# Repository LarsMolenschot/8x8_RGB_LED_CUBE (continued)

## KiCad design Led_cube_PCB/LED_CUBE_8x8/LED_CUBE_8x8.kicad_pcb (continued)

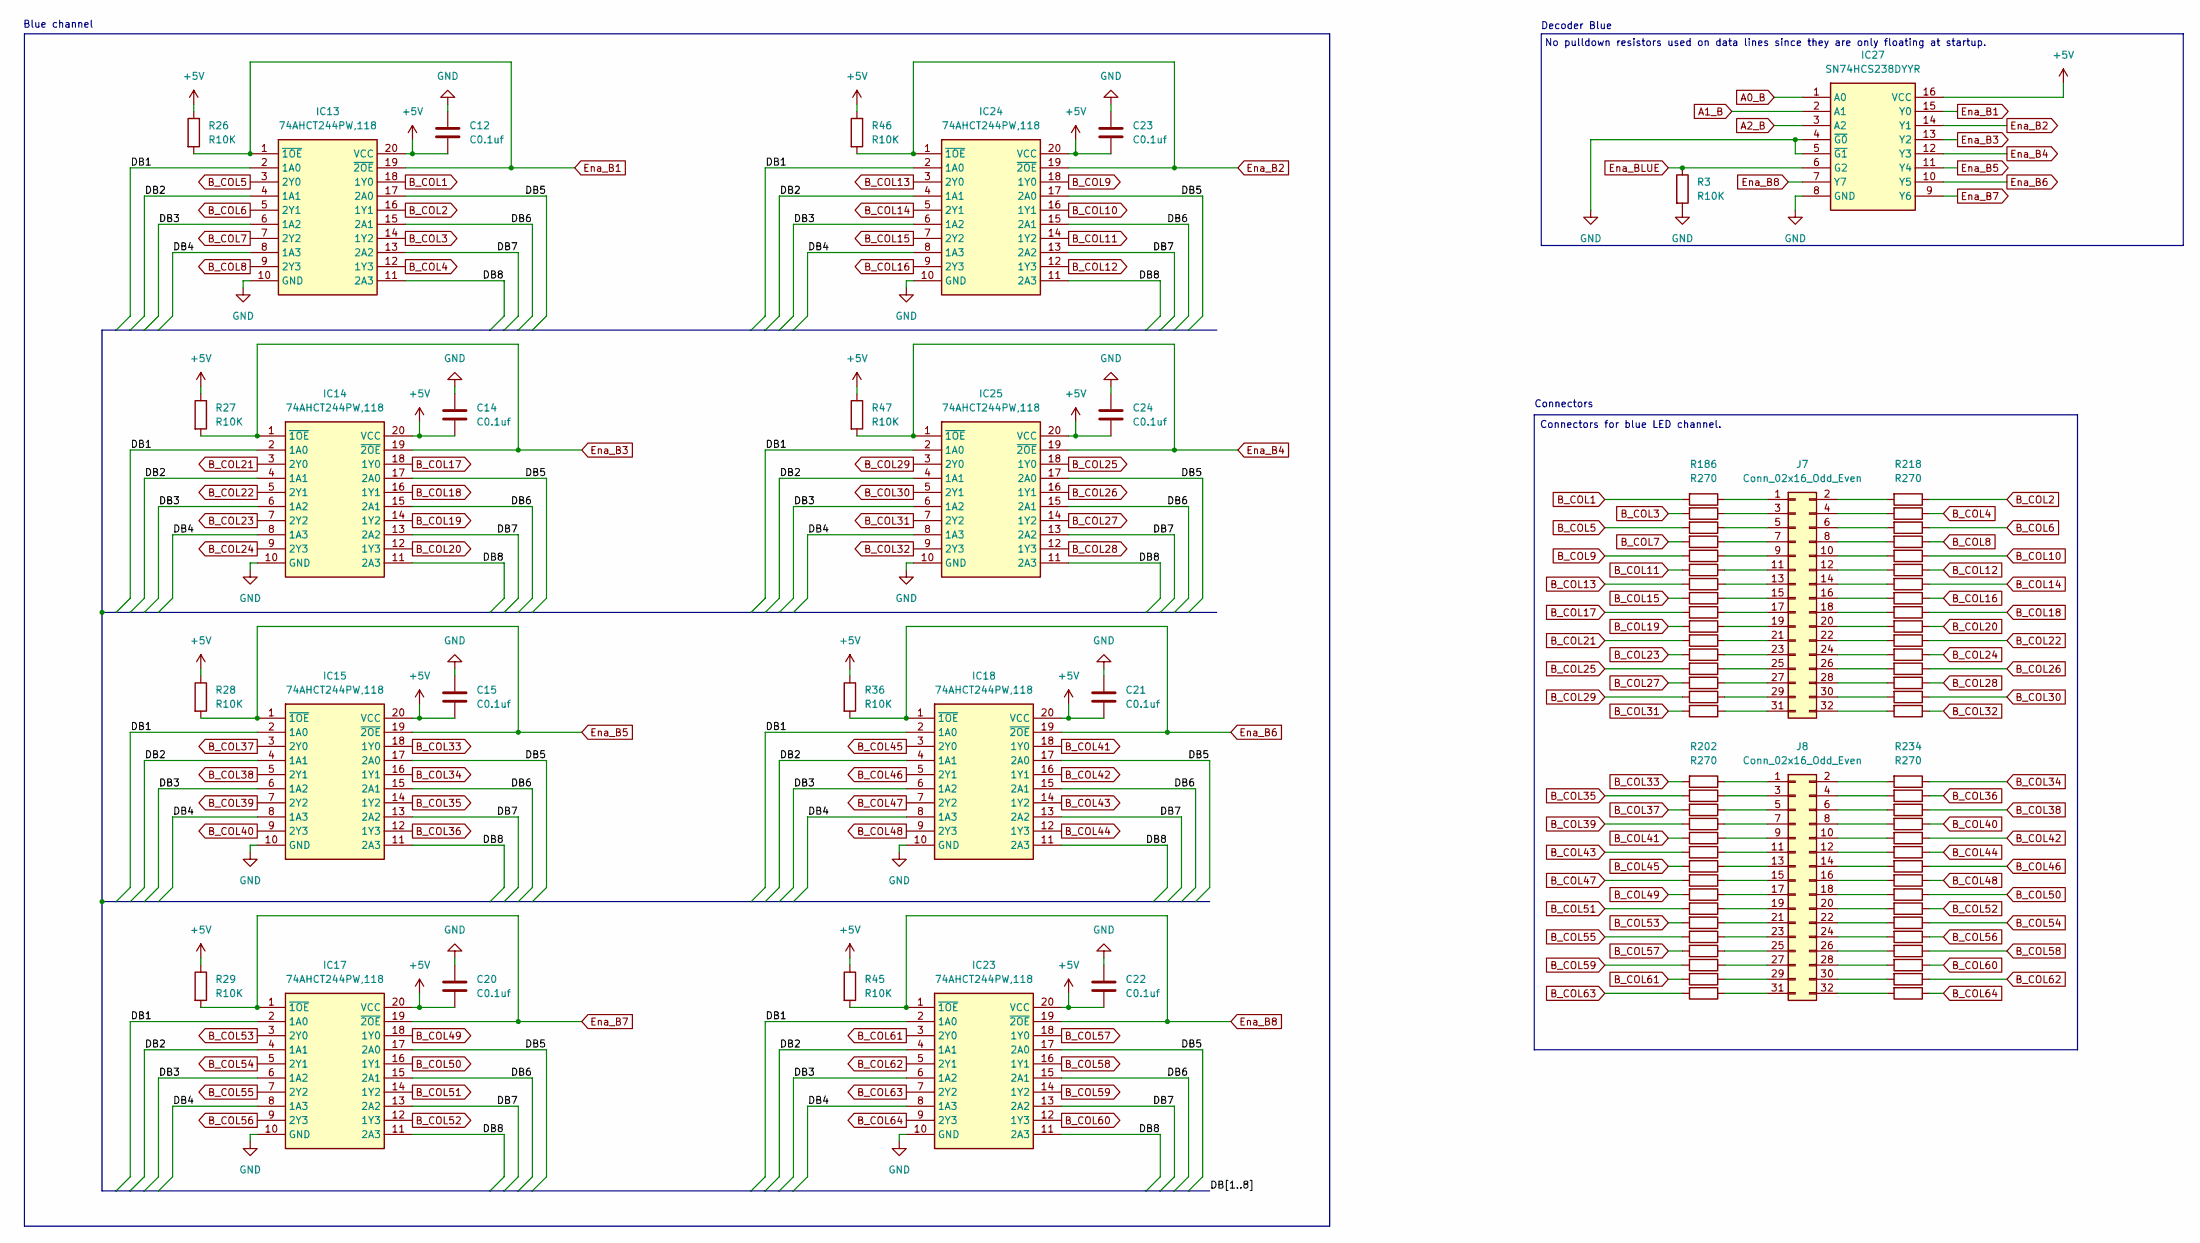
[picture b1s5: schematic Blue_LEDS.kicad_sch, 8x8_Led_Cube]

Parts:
C12, C14, C15, C20, C21, C22, C23, C24: C0.1uf; C_0603_1608Metric_Pad1.08x0.95mm_HandSolder
IC13, IC14, IC15, IC17, IC18, IC23, IC24, IC25: 74AHCT244PW,118; SOP65P640X110-20N; Mouser Part Number 771-AHCT244PW118
IC27: SN74HCS238DYYR; SOP50P326X110-16N; Mouser Part Number 595-SN74HCS238DYYR
J7, J8: Conn_02x16_Odd_Even; PinSocket_2x16_P2.54mm_Vertical
R3, R26, R27, R28, R29, R36, R45, R46, R47: R10K; R_0603_1608Metric_Pad0.98x0.95mm_HandSolder
R186, R187, R188, R189, R190, R191, R192, R193, R194, R195, R196, R197, R198, R199, R200, R201, R202, R203, R204, R205, R206, R207, R208, R209, R210, R211, R212, R213, R214, R215, R216, R217, R218, R219, R220, R221, R222, R223, R224, R225, R226, R227, R228, R229, R230, R231, R232, R233, R234, R235, R236, R237, R238, R239, R240, R241, R242, R243, R244, R245, R246, R247, R248, R249: R270; R_0603_1608Metric_Pad0.98x0.95mm_HandSolder

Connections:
+5V: C12.2, C14.2, C15.2, C20.2, C21.2, C22.2, C23.2, C24.1, IC13.20 (VCC), IC14.20 (VCC), IC15.20 (VCC), IC17.20 (VCC), IC18.20 (VCC), IC23.20 (VCC), IC24.20 (VCC), IC25.20 (VCC), IC27.16 (VCC), R26.1, R27.1, R28.1, R29.1, R36.1, R45.1, R46.1, R47.1; also elsewhere on the board
/Blue LED's/DB1: IC13.2 (1A0), IC14.2 (1A0), IC15.2 (1A0), IC17.2 (1A0), IC18.2 (1A0), IC23.2 (1A0), IC24.2 (1A0), IC25.2 (1A0)
/Blue LED's/DB2: IC13.4 (1A1), IC14.4 (1A1), IC15.4 (1A1), IC17.4 (1A1), IC18.4 (1A1), IC23.4 (1A1), IC24.4 (1A1), IC25.4 (1A1)
/Blue LED's/DB3: IC13.6 (1A2), IC14.6 (1A2), IC15.6 (1A2), IC17.6 (1A2), IC18.6 (1A2), IC23.6 (1A2), IC24.6 (1A2), IC25.6 (1A2)
/Blue LED's/DB4: IC13.8 (1A3), IC14.8 (1A3), IC15.8 (1A3), IC17.8 (1A3), IC18.8 (1A3), IC23.8 (1A3), IC24.8 (1A3), IC25.8 (1A3)
/Blue LED's/DB5: IC13.17 (2A0), IC14.17 (2A0), IC15.17 (2A0), IC17.17 (2A0), IC18.17 (2A0), IC23.17 (2A0), IC24.17 (2A0), IC25.17 (2A0)
/Blue LED's/DB6: IC13.15 (2A1), IC14.15 (2A1), IC15.15 (2A1), IC17.15 (2A1), IC18.15 (2A1), IC23.15 (2A1), IC24.15 (2A1), IC25.15 (2A1)
/Blue LED's/DB7: IC13.13 (2A2), IC14.13 (2A2), IC15.13 (2A2), IC17.13 (2A2), IC18.13 (2A2), IC23.13 (2A2), IC24.13 (2A2), IC25.13 (2A2)
/Blue LED's/DB8: IC13.11 (2A3), IC14.11 (2A3), IC15.11 (2A3), IC17.11 (2A3), IC18.11 (2A3), IC23.11 (2A3), IC24.11 (2A3), IC25.11 (2A3)
A0_B: IC27.1 (A0); also elsewhere on the board
A1_B: IC27.2 (A1); also elsewhere on the board
A2_B: IC27.3 (A2); also elsewhere on the board
B_COL1: IC13.18 (1Y0), R186.2
B_COL2: IC13.16 (1Y1), R218.1
B_COL3: IC13.14 (1Y2), R187.2
B_COL4: IC13.12 (1Y3), R219.1
B_COL5: IC13.3 (2Y0), R188.2
B_COL6: IC13.5 (2Y1), R220.1
B_COL7: IC13.7 (2Y2), R189.2
B_COL8: IC13.9 (2Y3), R221.1
B_COL9: IC24.18 (1Y0), R190.2
B_COL10: IC24.16 (1Y1), R222.1
B_COL11: IC24.14 (1Y2), R191.2
B_COL12: IC24.12 (1Y3), R223.1
B_COL13: IC24.3 (2Y0), R192.2
B_COL14: IC24.5 (2Y1), R224.1
B_COL15: IC24.7 (2Y2), R193.2
B_COL16: IC24.9 (2Y3), R225.1
B_COL17: IC14.18 (1Y0), R194.2
B_COL18: IC14.16 (1Y1), R226.1
B_COL19: IC14.14 (1Y2), R195.2
B_COL20: IC14.12 (1Y3), R227.1
B_COL21: IC14.3 (2Y0), R196.2
B_COL22: IC14.5 (2Y1), R228.1
B_COL23: IC14.7 (2Y2), R197.2
B_COL24: IC14.9 (2Y3), R229.1
B_COL25: IC25.18 (1Y0), R198.2
B_COL26: IC25.16 (1Y1), R230.1
B_COL27: IC25.14 (1Y2), R199.2
B_COL28: IC25.12 (1Y3), R231.1
B_COL29: IC25.3 (2Y0), R200.2
B_COL30: IC25.5 (2Y1), R232.1
B_COL31: IC25.7 (2Y2), R201.2
B_COL32: IC25.9 (2Y3), R233.1
B_COL33: IC15.18 (1Y0), R202.2
B_COL34: IC15.16 (1Y1), R234.1
B_COL35: IC15.14 (1Y2), R203.2
B_COL36: IC15.12 (1Y3), R235.1
B_COL37: IC15.3 (2Y0), R204.2
B_COL38: IC15.5 (2Y1), R236.1
B_COL39: IC15.7 (2Y2), R205.2
B_COL40: IC15.9 (2Y3), R237.1
B_COL41: IC18.18 (1Y0), R206.2
B_COL42: IC18.16 (1Y1), R238.1
B_COL43: IC18.14 (1Y2), R207.2
B_COL44: IC18.12 (1Y3), R239.1
B_COL45: IC18.3 (2Y0), R208.2
B_COL46: IC18.5 (2Y1), R240.1
B_COL47: IC18.7 (2Y2), R209.2
B_COL48: IC18.9 (2Y3), R241.1
B_COL49: IC17.18 (1Y0), R210.2
B_COL50: IC17.16 (1Y1), R242.1
B_COL51: IC17.14 (1Y2), R211.2
B_COL52: IC17.12 (1Y3), R243.1
B_COL53: IC17.3 (2Y0), R212.2
B_COL54: IC17.5 (2Y1), R244.1
B_COL55: IC17.7 (2Y2), R213.2
B_COL56: IC17.9 (2Y3), R245.1
B_COL57: IC23.18 (1Y0), R214.2
B_COL58: IC23.16 (1Y1), R246.1
B_COL59: IC23.14 (1Y2), R215.2
B_COL60: IC23.12 (1Y3), R247.1
B_COL61: IC23.3 (2Y0), R216.2
B_COL62: IC23.5 (2Y1), R248.1
B_COL63: IC23.7 (2Y2), R217.2
B_COL64: IC23.9 (2Y3), R249.1
Ena_B1: IC13.1 (~1OE), IC13.19 (~2OE), IC27.15 (Y0), R26.2
Ena_B2: IC24.1 (~1OE), IC24.19 (~2OE), IC27.14 (Y1), R46.2
Ena_B3: IC14.1 (~1OE), IC14.19 (~2OE), IC27.13 (Y2), R27.2
Ena_B4: IC25.1 (~1OE), IC25.19 (~2OE), IC27.12 (Y3), R47.2
Ena_B5: IC15.1 (~1OE), IC15.19 (~2OE), IC27.11 (Y4), R28.2
Ena_B6: IC18.1 (~1OE), IC18.19 (~2OE), IC27.10 (Y5), R36.2
Ena_B7: IC17.1 (~1OE), IC17.19 (~2OE), IC27.9 (Y6), R29.2
Ena_B8: IC23.1 (~1OE), IC23.19 (~2OE), IC27.7 (Y7), R45.2
Ena_BLUE: IC27.6 (G2), R3.1
GND: C12.1, C14.1, C15.1, C20.1, C21.1, C22.1, C23.1, C24.2, IC13.10 (GND), IC14.10 (GND), IC15.10 (GND), IC17.10 (GND), IC18.10 (GND), IC23.10 (GND), IC24.10 (GND), IC25.10 (GND), IC27.4 (~G0), IC27.5 (~G1), IC27.8 (GND), R3.2; also elsewhere on the board
unnamed: J7.1, R186.1
unnamed: J7.2, R218.2
unnamed: J7.3, R187.1
unnamed: J7.4, R219.2
unnamed: J7.5, R188.1
unnamed: J7.6, R220.2
unnamed: J7.7, R189.1
unnamed: J7.8, R221.2
unnamed: J7.9, R190.1
unnamed: J7.10, R222.2
unnamed: J7.11, R191.1
unnamed: J7.12, R223.2
unnamed: J7.13, R192.1
unnamed: J7.14, R224.2
unnamed: J7.15, R193.1
unnamed: J7.16, R225.2
unnamed: J7.17, R194.1
unnamed: J7.18, R226.2
unnamed: J7.19, R195.1
unnamed: J7.20, R227.2
unnamed: J7.21, R196.1
unnamed: J7.22, R228.2
unnamed: J7.23, R197.1
unnamed: J7.24, R229.2
unnamed: J7.25, R198.1
unnamed: J7.26, R230.2
unnamed: J7.27, R199.1
unnamed: J7.28, R231.2
unnamed: J7.29, R200.1
unnamed: J7.30, R232.2
unnamed: J7.31, R201.1
unnamed: J7.32, R233.2
unnamed: J8.1, R202.1
unnamed: J8.2, R234.2
unnamed: J8.3, R203.1
unnamed: J8.4, R235.2
unnamed: J8.5, R204.1
unnamed: J8.6, R236.2
unnamed: J8.7, R205.1
unnamed: J8.8, R237.2
unnamed: J8.9, R206.1
unnamed: J8.10, R238.2
unnamed: J8.11, R207.1
unnamed: J8.12, R239.2
unnamed: J8.13, R208.1
unnamed: J8.14, R240.2
unnamed: J8.15, R209.1
unnamed: J8.16, R241.2
unnamed: J8.17, R210.1
unnamed: J8.18, R242.2
unnamed: J8.19, R211.1
unnamed: J8.20, R243.2
unnamed: J8.21, R212.1
unnamed: J8.22, R244.2
unnamed: J8.23, R213.1
unnamed: J8.24, R245.2
unnamed: J8.25, R214.1
unnamed: J8.26, R246.2
unnamed: J8.27, R215.1
unnamed: J8.28, R247.2
unnamed: J8.29, R216.1
unnamed: J8.30, R248.2
unnamed: J8.31, R217.1
unnamed: J8.32, R249.2

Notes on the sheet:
No pulldown resistors used on data lines since they are only floating at startup.
Blue channel
Connectors
Decoder Blue
Connectors for blue LED channel.

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
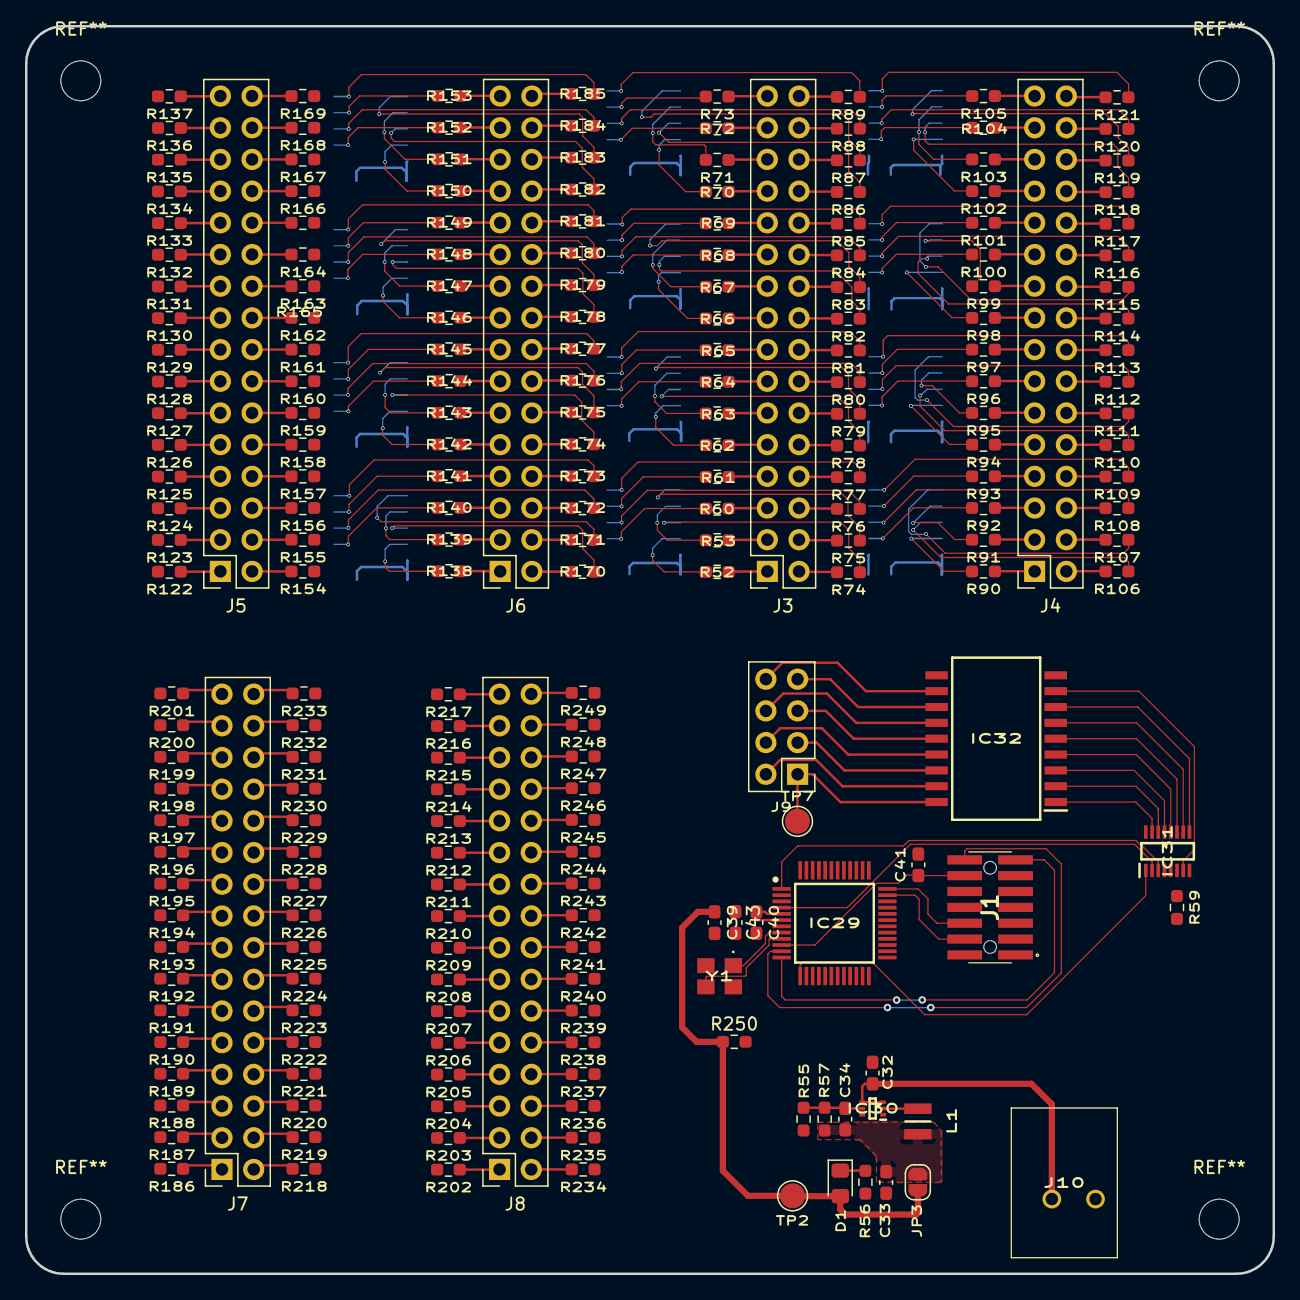
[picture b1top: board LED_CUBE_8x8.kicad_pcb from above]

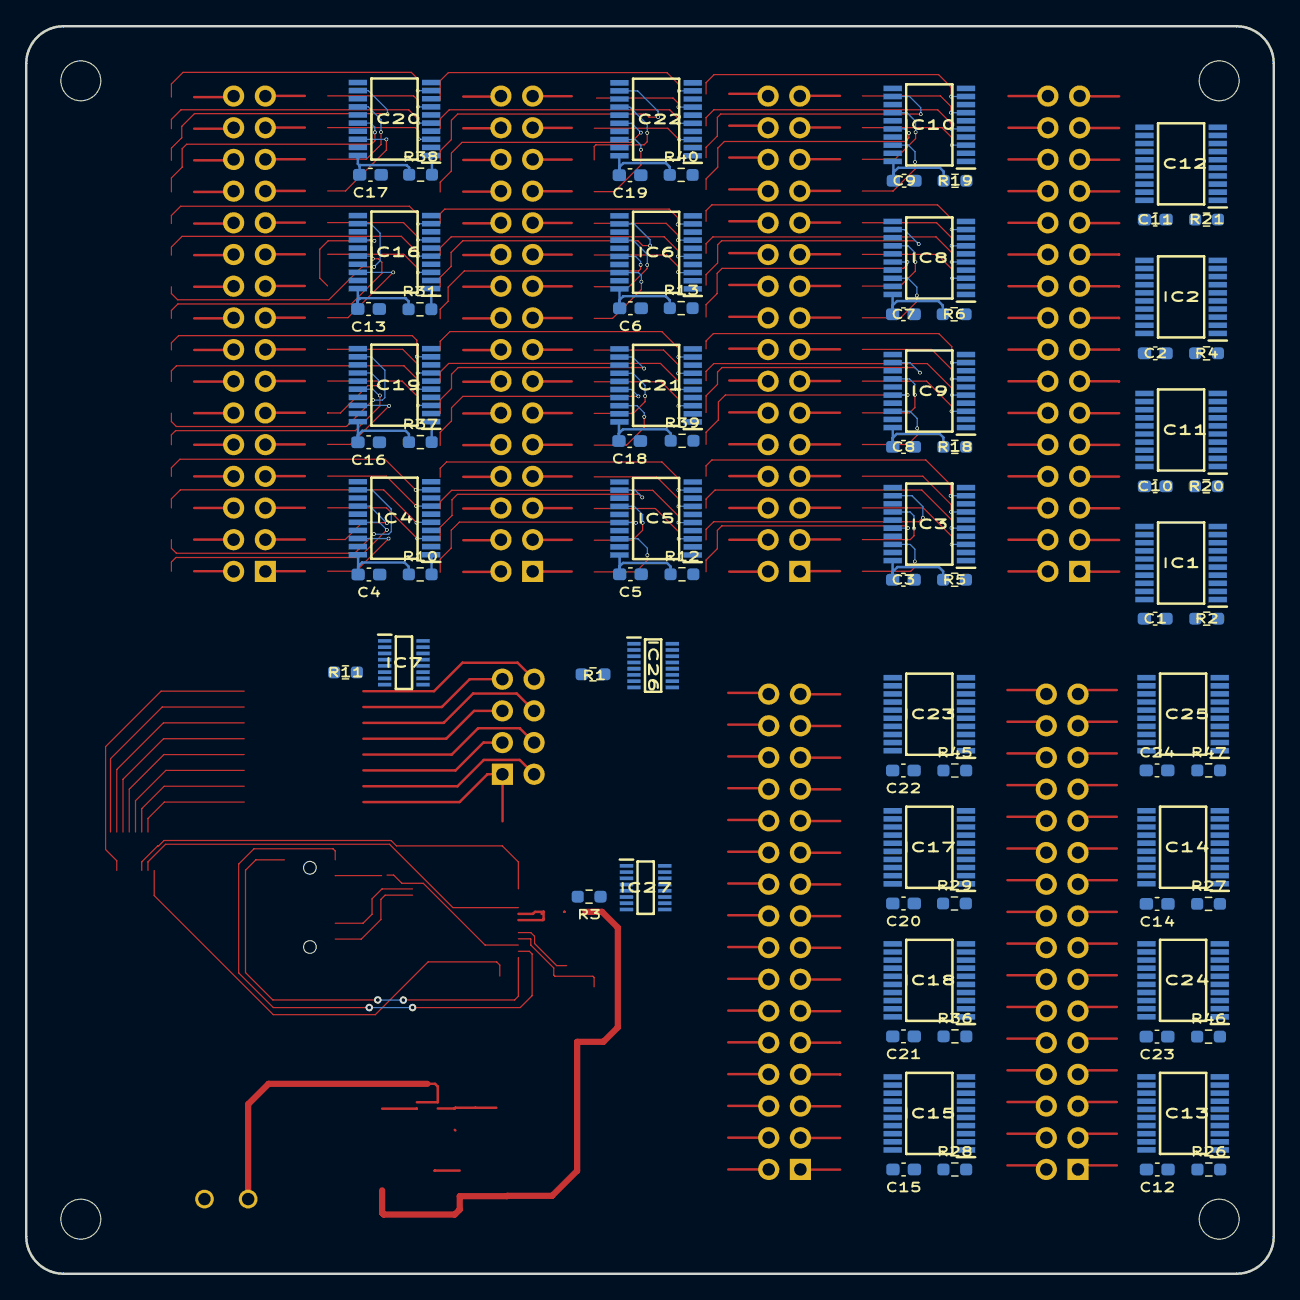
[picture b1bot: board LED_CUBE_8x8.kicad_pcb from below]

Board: 4 copper layers, 100.0 x 100.0 mm, 301 parts (78 on the bottom side), 478 nets.

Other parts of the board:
R250: R10K; R_0603_1608Metric_Pad0.98x0.95mm_HandSolder

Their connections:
+3.3V: R250.1; also elsewhere on the board
NRST: R250.2; also elsewhere on the board

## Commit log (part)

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2025-07-20 added initial KICAD files in addition with the samasyc parts which include the symbols and footprints for the various IC's.
2025-07-20 changed KICAD symbol and footprint libraries to use local path relative to project folder.
2025-07-20 cleaning repository after gitignore
2025-07-20 restoring KICAD project files
2025-07-20 added datasheets of the IC's used for the PCB
2025-07-23 added the decoder and buffer IC's to the schematic.
2025-07-26 changed buffer to a 5V tolerant one and worked on the schematic.
2025-07-26 Made progress on schematic red channel multiplexing almost finished.
2025-07-27 Finished the schematic for the red green and blue color multiplexing.
2025-07-31 added power schematic and updated labels to correct type e.g. output, input
2025-08-04 added 3.3V power supply for microcontroller and started on STM schematic.
2025-08-31 WIP: need to add connectors for the LED channels
2025-09-27 WIP: added layer select schematic
2025-10-01 added connector and current limiting resistors of the RED channel.
2026-03-13 added spice simulations folder, For simulating transients effect on the power buck converter. Also finished layer select in eeschema.
2026-04-18 updated to KICAD v10
2026-04-18 removed the untitled schematic
2026-04-18 Added test points and solder jumpers
